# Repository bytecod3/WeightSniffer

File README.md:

# WeightSniffer
Device to interface digital weight meter to POS systems

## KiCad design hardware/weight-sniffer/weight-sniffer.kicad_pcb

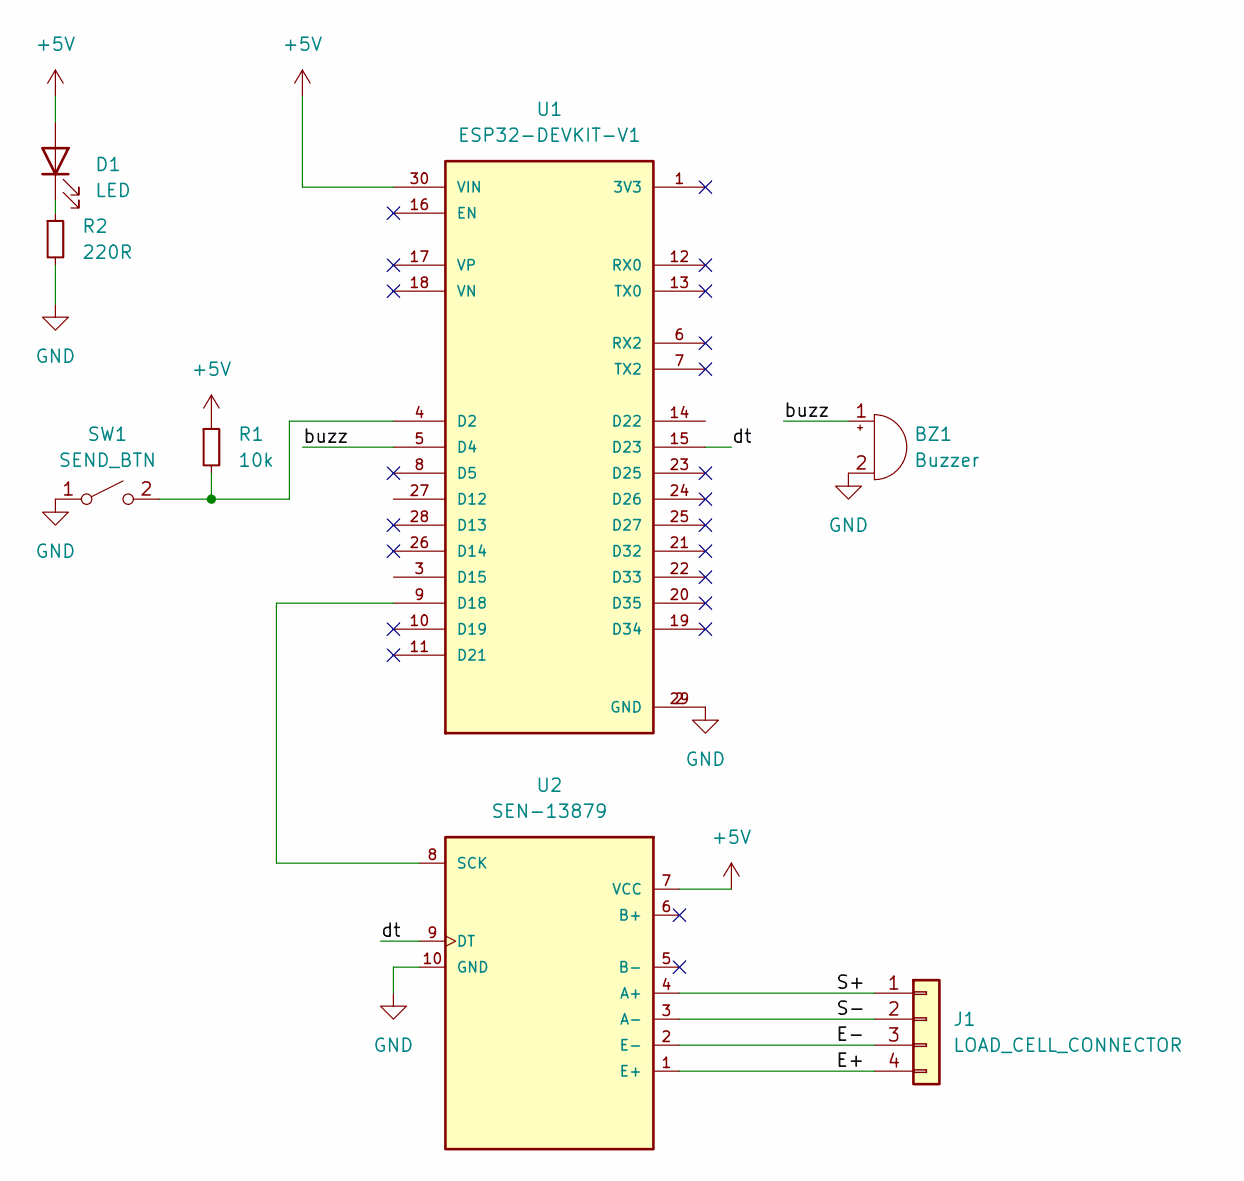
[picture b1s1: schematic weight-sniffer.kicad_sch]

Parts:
BZ1: Buzzer; Buzzer_D14mm_H7mm_P10mm
D1: LED; LED_D3.0mm
J1: LOAD_CELL_CONNECTOR; PinHeader_1x04_P2.54mm_Vertical
R1: 10k; R_Axial_DIN0204_L3.6mm_D1.6mm_P7.62mm_Horizontal
R2: 220R; R_Axial_DIN0204_L3.6mm_D1.6mm_P7.62mm_Horizontal
SW1: SEND_BTN; PinHeader_1x02_P2.54mm_Vertical
U1: ESP32-DEVKIT-V1; MODULE_ESP32_DEVKIT_V1; PARTREV N/A
U2: SEN-13879; SPARKFUN_SEN-13879

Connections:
+5V: D1.2 (A), R1.1, U1.30 (VIN), U2.7 (VCC)
/E+: J1.4, U2.1 (E+)
/E-: J1.3, U2.2 (E-)
/S+: J1.1, U2.4 (A+)
/S-: J1.2, U2.3 (A-)
/buzz: BZ1.1 (+), U1.5 (D4)
/dt: U1.15 (D23), U2.9 (DT)
GND: BZ1.2 (-), R2.2, SW1.1 (A), U1.2 (GND), U1.29 (GND), U2.10 (GND)
unnamed: D1.1 (K), R2.1
unnamed: R1.2, SW1.2 (B), U1.4 (D2)
unnamed: U1.9 (D18), U2.8 (SCK)

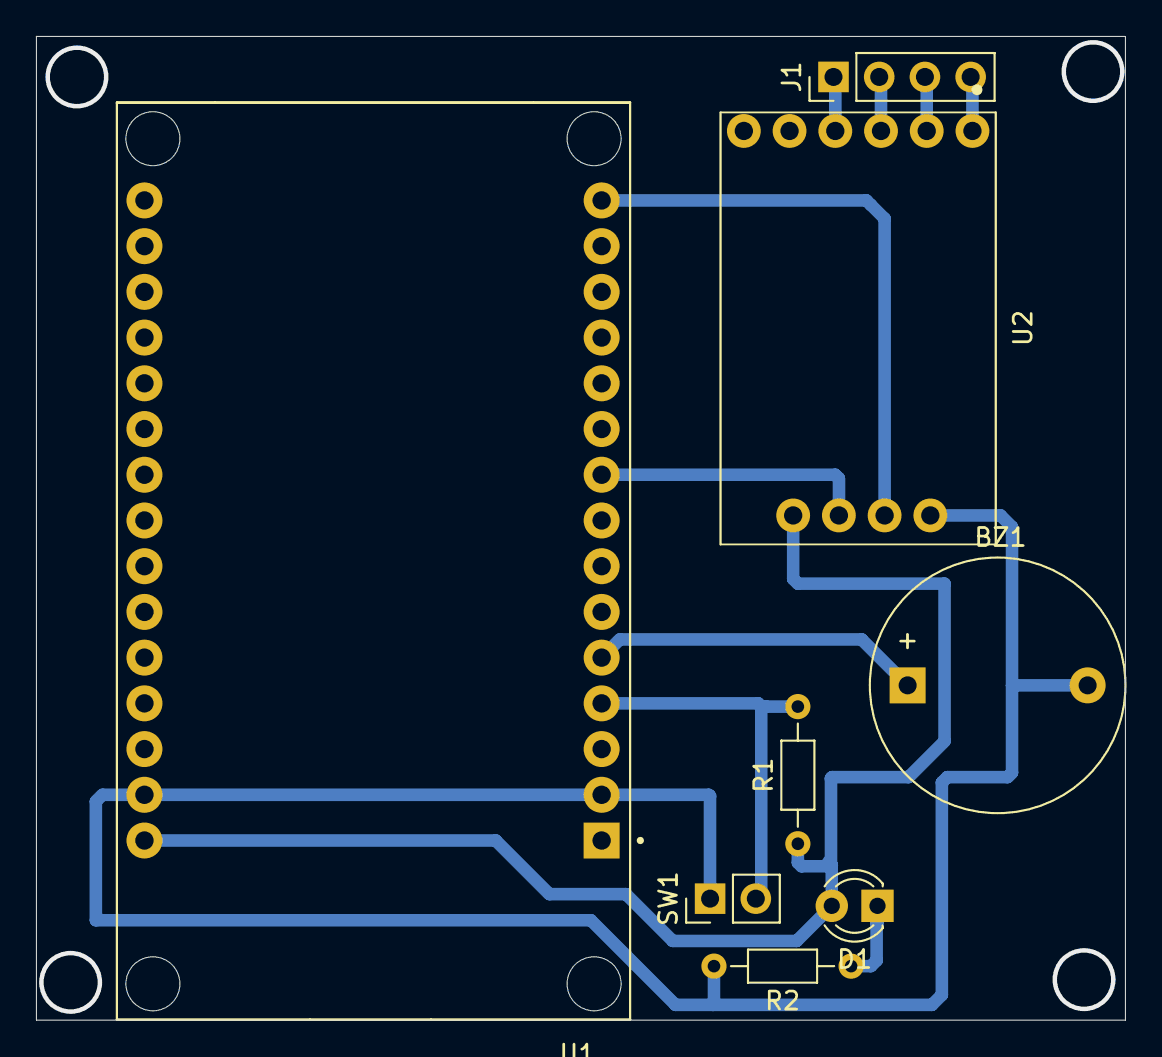
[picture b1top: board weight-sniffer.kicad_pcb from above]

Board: 2 copper layers, 60.5 x 54.7 mm, 8 parts (0 on the bottom side), 11 nets.

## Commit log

2024-10-15 adds espidf project structure
2024-10-15 added button ISR
2024-10-15 footprint assignment
2024-10-15 adds routed tracks
2024-10-19 adds buzz interval
2024-10-19 adds pio sniffer
